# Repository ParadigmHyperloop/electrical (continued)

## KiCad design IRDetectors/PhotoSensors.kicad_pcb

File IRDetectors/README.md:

# About this Board

* **Owner:** @edhurtig
* **Status:** `Build`
* **Topic:** Research

## Design Abstract 

In the most basic sense, this board is an Arduino with support for 2 modulated IR emitters and paired receivers. They are essentially smart IR proximity sensors. 

## Purpose

These boards are intended to detect vertical strips (4" wide) that are placed every 100' on the hypertube walls. These strips are useful for navigation purposes and tell the pod where it is in the tube.

These boards are also somewhat of a prototype for a localized control module for subsystems like #brakes where a local uC receives commands from the main flight computer, but locally is the one responsible for controlling the state of the brake control solenoids, monitoring pressures and temperatures, etc.

## Tech Specs

- **Microcontroller** Atmega32U4
- **Communication** 1 Micro USB, 1 ISP Header, 1 RS485 bus, I2C, (maybe) CANbus
- **Sensors** 2 IR Emitters, 2 IR Receivers. Local hardware-based 36Khz IR modulator.
- **Expansion Headers** All unused Atmega inputs and outputs routed to an expansion header

### RS485 Details
There are 3 ports that all share the RS485 connection: 2x Ethernet jacks (for daisy chain), 1x 4 pin Phoenix contact port

### Power Details

This board is a 5V logic level board. The board may be powered over USB or via an external power source. The external power source is recommended at 5.5V. Do not exceed 12V on any of the external power inputs.

### External Power Inputs

Power may be supplied through the 2 pin Phoenix Contact Power Connector as labeled on the board's silkscreen.

Alternatively, power may be supplied via the RJ45 jacks by supplying 5.5-12V on pin 8, and Ground on pin 7.  The jumpers for VCOM power and VCOM GND must be stuffed in order to enable power via the Ethernet ports.

**Do not plug these boards into a standard ethernet switch, behavior is undefined**

### On-Board Documentation (Silkscreen)
```
5V Logic
VCC Regulated 5V
VCOM Recommended 5.5V

Ethernet Pinout:
1-2: RS485 RX - / +
3: External IR Sync
4-5: RS485 TX - / +
6: Passthrough
7: VCOM - (Ground)
8: VCOM + (5-12V DC)

VCOM PWR set jumpers 
GND EN & VCOM EN 
```
## Status

- **Rev 1A** was ordered and lost in transit 😢 
- **Rev 1B** was ordered and partially assembled. The first board is currently in a state were it powers on. Next step is to plug in an ISP and flash a bootloader onto the Atmega.

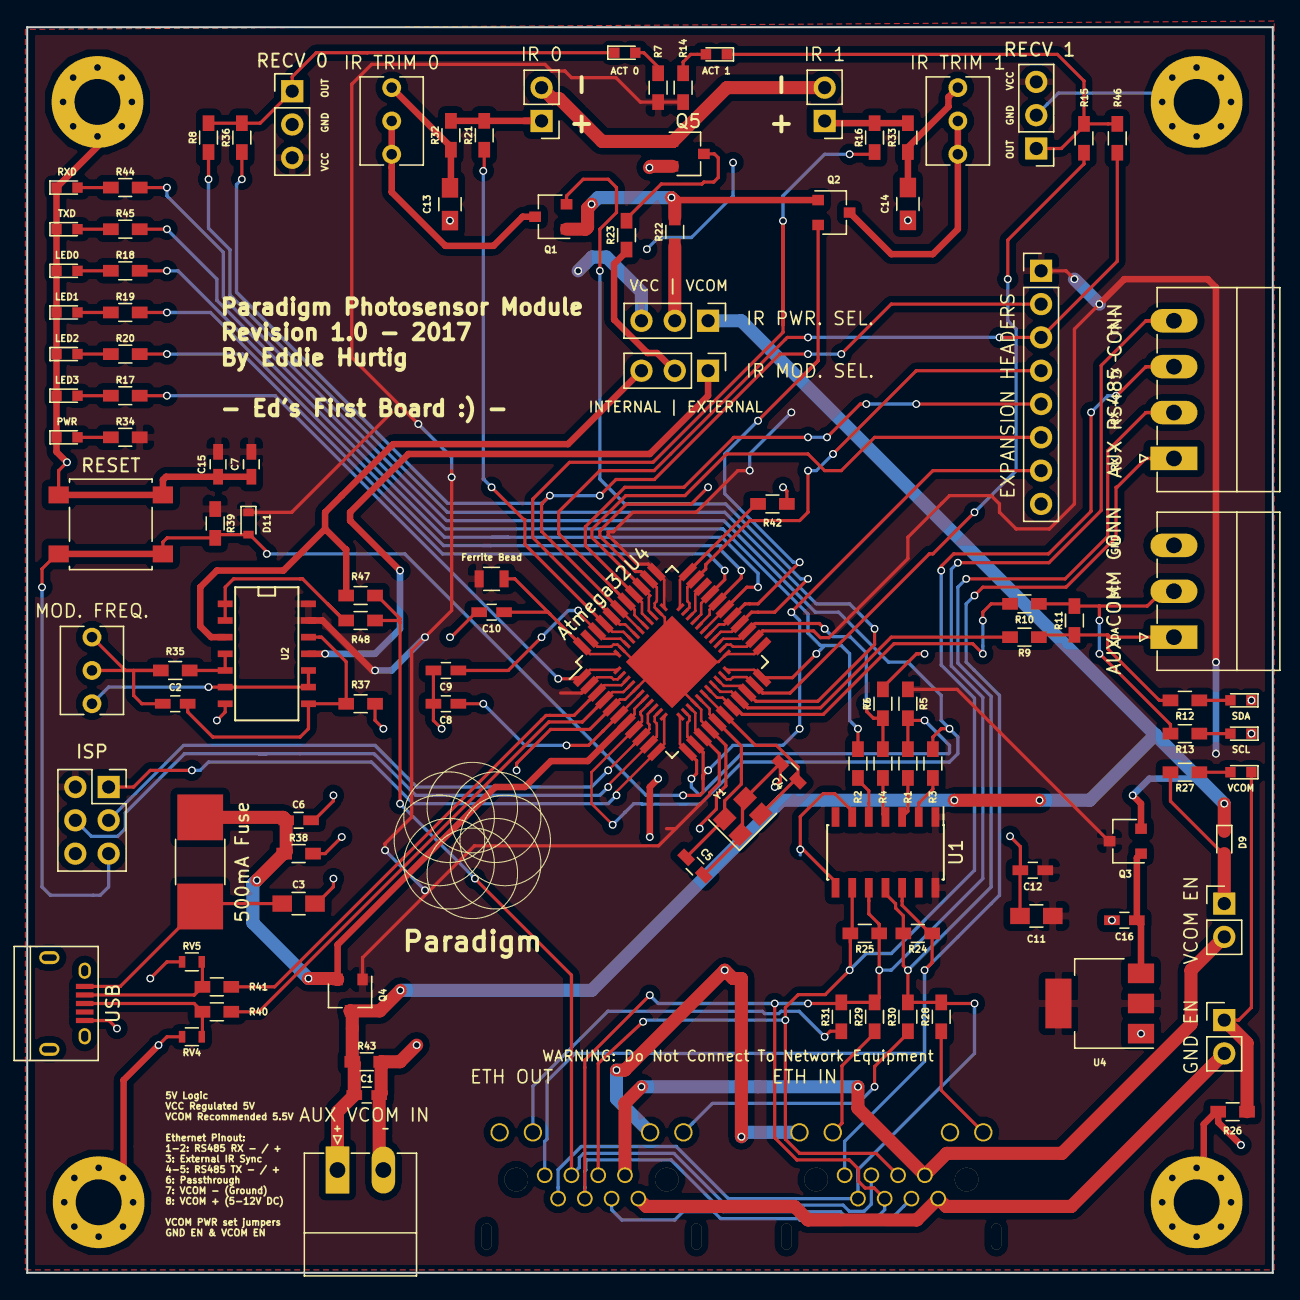
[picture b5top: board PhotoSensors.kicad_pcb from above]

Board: 2 copper layers, 95.0 x 95.0 mm, 112 parts (0 on the bottom side), 92 nets.

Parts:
500mA Fuse: 500mA; R_1812_HandSoldering
ACT 0: D0_ACT; LED_0603
ACT 1: D1_ACT; LED_0603
AUX COMM CONN: I2C _CONN; PhoenixContact_MC-G_03x3.50mm_Angled
AUX RS485 CONN: RS485_CONN; PhoenixContact_MC-G_04x3.50mm_Angled
AUX VCOM IN: PWR_IN; PhoenixContact_MC-G_02x3.50mm_Angled
Atmega32U4: ATMEGA32U4RC-A; QFN-44_7x7mm_Combined_TQFP-44_10x10mm_Pitch0.8mm
C1, C2: 10n; C_0603_HandSoldering
C3, C11: 22u; C_0805_HandSoldering
C4, C5: 22p; C_0603_HandSoldering
C6, C7, C9, C12, C15, C16: 100n; C_0603_HandSoldering
C8, C10: 1u; C_0603_HandSoldering
C13, C14: 10u; C_0805_HandSoldering
D9: D_VCOM; D_0603
D11: D_RST; D_0603
EXPANSION HEADERS: CONN_01X08; Pin_Header_Straight_1x08_Pitch2.54mm
Ferrite Bead: Ferrite_Bead; R_0805
GND EN: GND_EN; Pin_Header_Straight_1x02_Pitch2.54mm
IR 0: CONN_IR0; Pin_Header_Straight_1x02_Pitch2.54mm
IR 1: CONN_IR1; Pin_Header_Straight_1x02_Pitch2.54mm
IR MOD. SEL.: IR_SYNC_SELECT; Pin_Header_Straight_1x03_Pitch2.54mm
IR PWR. SEL.: Emitter Current Source; Pin_Header_Straight_1x03_Pitch2.54mm
IR TRIM 0, IR TRIM 1: RP500; Potentiometer_Trimmer_Vishay_T73XW_Vertical
ISP: ISP; Socket_Strip_Straight_2x03_Pitch2.54mm
J1, J2: RJ45_LEDS; RJ45_8P8C_90DEG_LEDs
LED0: LED1; LED_0603
LED1: LED2; LED_0603
LED2: LED3; LED_0603
LED3: LED0; LED_0603
MOD. FREQ.: POT_TRIM; Potentiometer_Trimmer_Vishay_T73XW_Vertical
PWR: PWR_LED; LED_0603
Q1, Q2, Q4: FDN340PCT-ND; SC-59
Q3: FDN340PCT; SC-59
Q5: Q_PMOS_SDG; SC-59
R1, R2, R3, R4, R16, R21, R23, R26, R32, R33, R36, R46, R48: 0; R_0603_HandSoldering
R5, R6: 20k; R_0603_HandSoldering
R7, R12, R13, R14, R17, R18, R19, R20, R27, R28, R29, R30, R31, R34, R44, R45: 1k; R_0603_HandSoldering
R8, R15: 220; R_0603_HandSoldering
R9, R10, R11, R47: DNS; R_0603_HandSoldering
R22: 470; R_0603_HandSoldering
R24, R25: 120; R_0603_HandSoldering
R35: 100k; R_0603_HandSoldering
R37, R38, R39, R42, R43: 10k; R_0603_HandSoldering
R40, R41: 22R; R_0603_HandSoldering
RECV 0: CONN_PD0; Pin_Header_Straight_1x03_Pitch2.54mm
RECV 1: CONN_PD1; Pin_Header_Straight_1x03_Pitch2.54mm
RESET: RESET_BTN; SW_SPST_B3S-1000
RV4, RV5: CG0603MLC; R_0603
RXD: RX_LED; LED_0603
SCL: SCL; LED_0603
SDA: SDA; LED_0603
TXD: TX_LED; LED_0603
U1: MAX13432EETD; SOIC-14_3.9x8.7mm_Pitch1.27mm
U2: 7400; SOIC-14_N
U4: NCP1117ST50T3GOSCT; SOT-223
USB: USB_MICRO; USB_Micro-B
VCOM: VCOM_PWR; LED_0603
VCOM EN: VCOM_EN; Pin_Header_Straight_1x02_Pitch2.54mm
Y1: Crystal; Crystal_SMD_Abracon_ABM8G-4pin_3.2x2.5mm

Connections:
/ADC4: Atmega32U4.39, EXPANSION HEADERS.2, R36.1
/ADC5: Atmega32U4.38, EXPANSION HEADERS.3, R46.1
/Atmega/D+: Atmega32U4.4, R40.1
/Atmega/D-: Atmega32U4.3, R41.1
/Atmega/MISO: Atmega32U4.11, ISP.1
/Atmega/MOSI: Atmega32U4.10, ISP.4
/Atmega/PC7: Atmega32U4.32, EXPANSION HEADERS.4
/Atmega/PF6: Atmega32U4.37, EXPANSION HEADERS.5
/Atmega/PF7: Atmega32U4.36, EXPANSION HEADERS.6
/Atmega/SCK: Atmega32U4.9, ISP.3
/Atmega/XTAL1: Atmega32U4.17, C4.1, Y1.2
/Atmega/XTAL2: Atmega32U4.16, C5.1, Y1.4
/D0_OUT: ACT 0.1, R8.2, R36.2, RECV 0.1
/D1_OUT: ACT 1.1, R15.2, R46.2, RECV 1.1
/DE: Atmega32U4.12, R1.1, R5.1
/EXT_SYNC: J1.3, J2.3, R47.1, R48.1
/INT0: Atmega32U4.20, R8.1
/INT1: Atmega32U4.21, R15.1
/IR0_+: IR 0.1, R21.2, R32.2
/IR0_-: IR 0.2, IR 1.2, Q5.1
/IR0_ADC: Atmega32U4.41, R21.1
/IR0_SETPOINT: Atmega32U4.26, Q1.2
/IR1_+: IR 1.1, R16.1, R33.2
/IR1_ADC: Atmega32U4.40, R16.2
/IR1_SETPOINT: Atmega32U4.27, Q2.2
/LED0: Atmega32U4.1, R17.2
/LED1: Atmega32U4.28, R18.2
/LED2: Atmega32U4.29, R19.2
/LED3: Atmega32U4.30, R20.2
/RE: Atmega32U4.25, R4.1, R6.2
/RESET: Atmega32U4.13, D11.2, EXPANSION HEADERS.7, ISP.5, R39.2, RESET.2
/RS422_Transiever/DE: R1.2, U1.3
/RS422_Transiever/RE: R4.2, U1.4
/RS422_Transiever/RS485_RX_+: AUX RS485 CONN.2, J1.2, J2.2, R24.1, R28.2, R30.2, U1.11
/RS422_Transiever/RS485_RX_-: AUX RS485 CONN.1, J1.1, J2.1, R24.2, U1.12
/RS422_Transiever/RS485_TX_+: AUX RS485 CONN.4, J1.4, J2.4, R25.1, R29.2, R31.2, U1.10
/RS422_Transiever/RS485_TX_-: AUX RS485 CONN.3, J1.5, J2.5, R25.2, U1.9
/RS422_Transiever/RXD: R3.2, U1.2
/RS422_Transiever/TXD: R2.2, U1.5
/RXD: Atmega32U4.8, R3.1, R44.2
/SCL: Atmega32U4.18, R10.2
/SDA: Atmega32U4.19, R9.2
/TXD: Atmega32U4.22, R2.1, R45.2
GND: AUX COMM CONN.3, AUX VCOM IN.2, Atmega32U4.5, Atmega32U4.15, Atmega32U4.23, Atmega32U4.35, Atmega32U4.43, C1.2, C3.2, C4.2, C5.2, C6.2, C7.1, C8.2, C9.2, C10.2, C11.2, C12.2, C13.1, C14.1, C15.1, C16.2, EXPANSION HEADERS.8, ISP.6, J1.9, J1.11, J2.9, J2.11, LED0.1, LED1.1, LED2.1, LED3.1, PWR.1, Q5.2, R6.1, R26.2, R37.2, R38.2, R42.1, R43.1, RECV 0.2, RECV 1.2, RESET.1, RV4.1, RV5.1, RXD.1, SCL.1, SDA.1, TXD.1, U1.6, U1.8, U2.7, U4.1, USB.5, USB.6, Y1.1, Y1.3
unnamed: C2.1, MOD. FREQ..1, MOD. FREQ..2, R35.1
unnamed: C2.2, R37.1, U2.8, U2.12
unnamed: 500mA Fuse.2, C3.1, USB.1
unnamed: Atmega32U4.6, C8.1
unnamed: Atmega32U4.42, C9.1
unnamed: Atmega32U4.44, C10.1, Ferrite Bead.1
unnamed: C13.2, IR TRIM 0.3, R32.1
unnamed: C14.2, IR TRIM 1.3, R33.1
unnamed: C16.1, Q3.1, U4.3
unnamed: ACT 0.2, R7.2
unnamed: R12.2, SDA.2
unnamed: R13.2, SCL.2
unnamed: ACT 1.2, R14.2
unnamed: LED3.2, R17.1
unnamed: LED0.2, R18.1
unnamed: LED1.2, R19.1
unnamed: LED2.2, R20.1
unnamed: D9.2, R27.2, VCOM EN.1
unnamed: GND EN.1, R26.1, VCOM.1
unnamed: R27.1, VCOM.2
unnamed: PWR.2, R34.1
unnamed: R44.1, RXD.2
unnamed: R45.1, TXD.2
unnamed: MOD. FREQ..3, U2.6, U2.9, U2.10
unnamed: J1.7, J2.7, VCOM EN.2
unnamed: GND EN.2, J1.8, J2.8
unnamed: J1.10, R29.1
unnamed: J1.12, R28.1
unnamed: J2.10, R31.1
unnamed: J2.12, R30.1
unnamed: IR PWR. SEL..2, R22.1
unnamed: IR MOD. SEL..1, U2.11
unnamed: IR MOD. SEL..2, R23.1
unnamed: IR MOD. SEL..3, R47.2, U2.3
unnamed: AUX COMM CONN.1, R9.1, R11.1, R12.1
unnamed: AUX COMM CONN.2, R10.1, R11.2, R13.1
unnamed: R41.2, RV5.2, USB.2
unnamed: R40.2, RV4.2, USB.3
unnamed: Q1.1, Q2.1, R22.2
unnamed: IR TRIM 0.1, IR TRIM 0.2, Q1.3
unnamed: IR TRIM 1.1, IR TRIM 1.2, Q2.3
unnamed: Q5.3, R23.2
unnamed: R35.2, U2.4, U2.5
unnamed: Atmega32U4.33, R42.2
unnamed: R48.2, U2.1, U2.2
VCC: Atmega32U4.2, Atmega32U4.14, Atmega32U4.24, Atmega32U4.34, C7.2, C11.1, C12.1, C15.2, D11.1, EXPANSION HEADERS.1, Ferrite Bead.2, IR PWR. SEL..3, ISP.2, Q3.3, Q4.1, R5.2, R7.1, R14.1, R34.2, R39.1, RECV 0.3, RECV 1.3, U1.1, U1.14, U2.13, U2.14, U4.2, U4.4
VCOM: AUX VCOM IN.1, C1.1, D9.1, IR PWR. SEL..1, Q3.2, Q4.3, R43.2
VUSB: 500mA Fuse.1, Atmega32U4.7, C6.1, Q4.2, R38.1

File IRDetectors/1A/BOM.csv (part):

Component,Description,Part,References,Value,Footprint,Quantity Per PCB,Datasheet,Supporting,
1,Unpolarized capacitor,C,C6 C7 C9 C12 C15 C16,100n,C_0603_HandSoldering,6,https://www.digikey.com/product-detail/en/murata-electronics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,https://www.digikey.com/product-detail/en/murata-electronics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,
2,Unpolarized capacitor,C,C1 C2,10n,C_0603_HandSoldering,2,https://www.digikey.com/product-detail/en/murata-electronics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,https://www.digikey.com/product-detail/en/murata-electronics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,
3,Unpolarized capacitor,C,C13 C14,10u,C_0805_HandSoldering,2,https://www.digikey.com/product-detail/en/murata-electronics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,https://www.digikey.com/product-detail/en/murata-electronics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,
4,Unpolarized capacitor,C,C8 C10,1u,C_0603_HandSoldering,2,https://www.digikey.com/product-detail/en/samsung-electro-me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,https://www.digikey.com/product-detail/en/samsung-electro-me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,
5,Unpolarized capacitor,C,C4 C5,22p,C_0603_HandSoldering,2,https://www.digikey.com/product-detail/en/samsung-electro-me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,https://www.digikey.com/product-detail/en/samsung-electro-me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,
6,Polarised capacitor,CP,C11,22u,C_0805_HandSoldering,1,https://www.digikey.com/product-detail/en/avx-corporation/F9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,https://www.digikey.com/product-detail/en/avx-corporation/F9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,
7,Unpolarized capacitor,C,C3,22u,C_0805_HandSoldering,1,https://www.digikey.com/product-detail/en/samsung-electro-me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,https://www.digikey.com/product-detail/en/samsung-electro-me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,
8,LED generic,LED,D1,D0_ACT,LED_0603,1,https://www.digikey.com/product-detail/en/wurth-electronics-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,https://www.digikey.com/product-detail/en/wurth-electronics-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,
9,LED generic,LED,D4,D1_ACT,LED_0603,1,https://www.digikey.com/product-detail/en/wurth-electronics-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,https://www.digikey.com/product-detail/en/wurth-electronics-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,
10,Diode,D,D11,D_RST,D_0603,1,https://www.digikey.com/product-detail/en/avx-corporation/SD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,https://www.digikey.com/product-detail/en/avx-corporation/SD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,
11,Diode,D,D9,D_VCOM,D_0603,1,https://www.digikey.com/product-detail/en/avx-corporation/SD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,https://www.digikey.com/product-detail/en/avx-corporation/SD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,
12,LED generic,LED,D5,LED0,LED_0603,1,https://www.digikey.com/product-detail/en/wurth-electronics-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,https://www.digikey.com/product-detail/en/wurth-electronics-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,
13,LED generic,LED,D6,LED1,LED_0603,1,https://www.digikey.com/product-detail/en/wurth-electronics-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,https://www.digikey.com/product-detail/en/wurth-electronics-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,
14,LED generic,LED,D7,LED2,LED_0603,1,https://www.digikey.com/product-detail/en/wurth-electronics-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,https://www.digikey.com/product-detail/en/wurth-electronics-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,
15,LED generic,LED,D8,LED3,LED_0603,1,https://www.digikey.com/product-detail/en/wurth-electronics-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,https://www.digikey.com/product-detail/en/wurth-electronics-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,
16,LED generic,LED,D12,PWR_LED,LED_0603,1,https://www.digikey.com/product-detail/en/wurth-electronics-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,https://www.digikey.com/product-detail/en/wurth-electronics-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,
17,LED generic,LED,D13,RX_LED,LED_0603,1,https://www.digikey.com/product-detail/en/wurth-electronics-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,https://www.digikey.com/product-detail/en/wurth-electronics-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,
18,LED generic,LED,D3,SCL,LED_0603,1,https://www.digikey.com/product-detail/en/wurth-electronics-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,https://www.digikey.com/product-detail/en/wurth-electronics-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,
19,LED generic,LED,D2,SDA,LED_0603,1,https://www.digikey.com/product-detail/en/wurth-electronics-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,https://www.digikey.com/product-detail/en/wurth-electronics-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,
20,LED generic,LED,D14,TX_LED,LED_0603,1,https://www.digikey.com/product-detail/en/wurth-electronics-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,https://www.digikey.com/product-detail/en/wurth-electronics-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,
21,LED generic,LED,D10,VCOM_PWR,LED_0603,1,https://www.digikey.com/product-detail/en/wurth-electronics-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,https://www.digikey.com/product-detail/en/wurth-electronics-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,
22,"Fuse, generic",Fuse,F500,500mA,R_1812_HandSoldering,1,https://www.digikey.com/product-detail/en/bourns-inc/MF-MSMF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,https://www.digikey.com/product-detail/en/bourns-inc/MF-MSMF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,
23,Trim-Potentionmeter,POT_TRIM,FREQ1,POT_TRIM,Potentiometer_Trimmer_Vishay_T73XW_Vertical,1,https://www.digikey.com/product-detail/en/vishay-spectrol/M6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,https://www.digikey.com/product-detail/en/vishay-spectrol/M6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,
24,"RJ45, status leds",RJ45_LEDS,J1 J2,RJ45_LEDS,RJ45_8P8C_90DEG_LEDs,2,https://www.digikey.com/product-detail/en/amphenol-commercia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,https://www.digikey.com/product-detail/en/amphenol-commercia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,
25,"Dual Jumper, normally closed",Jumper_NC_Dual,JP3,Emitter Current Source,Pin_Header_Straight_1x03_Pitch2.54mm,1,https://www.digikey.com/product-detail/en/amphenol-fci/68000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,https://www.digikey.com/product-detail/en/amphenol-fci/68000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,
26,"Jumper, normally closed",Jumper_NC_Small,JP2,GND_EN,Pin_Header_Straight_1x02_Pitch2.54mm,1,https://www.digikey.com/product-detail/en/amphenol-fci/67996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,https://www.digikey.com/product-detail/en/amphenol-fci/67996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,
27,"Dual Jumper, normally closed",Jumper_NC_Dual,JP4,IR_SYNC_SELECT,Pin_Header_Straight_1x03_Pitch2.54mm,1,,,
28,"Jumper, normally closed",Jumper_NC_Small,JP1,VCOM_EN,Pin_Header_Straight_1x02_Pitch2.54mm,1,,,
29,Ferrite bead,Ferrite_Bead,MH2029-300Y1,Ferrite_Bead,R_0805,1,https://www.digikey.com/product-detail/en/bourns-inc/MH2029-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,https://www.digikey.com/product-detail/en/bourns-inc/MH2029-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,
30,"Connector, single row, 01x08",CONN_01X08,P4,CONN_01X08,Pin_Header_Straight_1x08_Pitch2.54mm,1,,,
31,"Connector, single row, 01x02",CONN_01X02,P6,CONN_IR0,Pin_Header_Straight_1x02_Pitch2.54mm,1,,,
32,"Connector, single row, 01x02",CONN_01X02,P5,CONN_IR1,Pin_Header_Straight_1x02_Pitch2.54mm,1,,,
33,"Connector, single row, 01x03",CONN_01X03,P2,CONN_PD0,Pin_Header_Straight_1x03_Pitch2.54mm,1,,,
34,"Connector, single row, 01x03",CONN_01X03,P1,CONN_PD1,Pin_Header_Straight_1x03_Pitch2.54mm,1,,,
35,"Connector, single row, 01x03",CONN_01X03,P3,I2C _CONN,PhoenixContact_MC-G_03x3.50mm_Angled,1,https://www.digikey.com/product-detail/en/molex-llc/03950210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,https://www.digikey.com/product-detail/en/molex-llc/03950210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,https://www.digikey.com/product-detail/en/molex-llc/03950000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
36,"Connector, double row, 02x03",CONN_02X03,P10,ISP,Socket_Strip_Straight_2x03_Pitch2.54mm,1,,,
37,"Connector, single row, 01x02",CONN_01X02,P7,PWR_IN,PhoenixContact_MC-G_02x3.50mm_Angled,1,https://www.digikey.com/product-detail/en/molex-llc/03950210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,https://www.digikey.com/product-detail/en/molex-llc/03950210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,https://www.digikey.com/product-detail/en/molex-llc/39500-00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
38,"Connector, single row, 01x04",CONN_01X04,P8,RS485_CONN,PhoenixContact_MC-G_04x3.50mm_Angled,1,https://www.digikey.com/product-detail/en/molex-llc/03950210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,https://www.digikey.com/product-detail/en/molex-llc/03950210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,https://www.digikey.com/product-detail/en/molex-llc/39500-00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
39,USB micro/mini connector,USB_OTG,P9,USB_MICRO,USB_Micro-B,1,https://www.digikey.com/product-detail/en/amphenol-fci/10118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,https://www.digikey.com/product-detail/en/amphenol-fci/10118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,
40,Transistor P-MOSFET with substrate diode (general),Q_PMOS_SDG,Q3,FDN340PCT,SC-59,1,https://www.digikey.com/product-detail/en/fairchild-on-semic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,https://www.digikey.com/product-detail/en/fairchild-on-semic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,
41,Transistor N-JFET (general),Q_NJFET_DGS,Q1 Q2,FDN340PCT-ND,SC-59,2,https://www.digikey.com/product-detail/en/fairchild-on-semic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,https://www.digikey.com/product-detail/en/fairchild-on-semic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,
42,Transistor P-MOSFET with substrate diode (general),Q_PMOS_SDG,Q4,FDN340PCT-ND,SC-59,1,https://www.digikey.com/product-detail/en/fairchild-on-semic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,https://www.digikey.com/product-detail/en/fairchild-on-semic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,
43,Resistor,R,R1 R2 R3 R4 R16 R21 R23 R26 R32 R33 R36 R46 R48,0,R_0603_HandSoldering,13,https://www.digikey.com/product-detail/en/yageo/RC0603JR-070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,https://www.digikey.com/product-detail/en/yageo/RC0603JR-070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,
44,Resistor,R,R35,100k,R_0603_HandSoldering,1,https://www.digikey.com/product-detail/en/yageo/RC0603JR-071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,https://www.digikey.com/product-detail/en/yageo/RC0603JR-071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,
45,Resistor,R,R37 R38 R39 R42 R43,10k,R_0603_HandSoldering,5,https://www.digikey.com/product-detail/en/yageo/RC0603JR-071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,https://www.digikey.com/product-detail/en/yageo/RC0603JR-071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,
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
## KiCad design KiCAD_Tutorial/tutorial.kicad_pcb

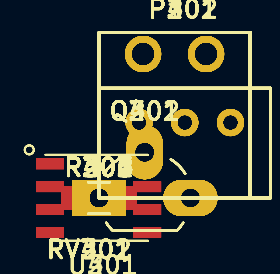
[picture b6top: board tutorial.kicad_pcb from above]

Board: 2 copper layers, 40 parts (0 on the bottom side), 32 nets, no tracks yet.

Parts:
P101, P201, P202, P301, P302, P401, P402: CONN_01X02; CONN_PHOENIX_1844210_2PIN
Q201, Q202, Q301, Q302, Q401, Q402: Transistor_PNP_MicroCommCo_2N3906; TO-92_Rugged_swap2and3
R201, R204, R301, R304, R401, R404: 1k; R_0805_HandSoldering
R202, R205, R302, R305, R402, R405: 10k; R_0805_HandSoldering
R203, R206, R303, R306, R403, R406: 10; R_0805_HandSoldering
RV201, RV202, RV301, RV302, RV401, RV402: 5k; BOURNS_MULTITURNPOT_3PIN
U201, U301, U401: OpAmp_TexasInstruments_LM358DR; SOIC-8_3.10x3.10_Pitch0.65mm

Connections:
+5V: P101.1, R203.1, R206.1, R303.1, R306.1, R403.1, R406.1, RV201.1, RV202.1, RV301.1, RV302.1, RV401.1, RV402.1, U201.8, U301.8, U401.8
GND: P101.2, P201.2, P202.2, P301.2, P302.2, P401.2, P402.2, R202.2, R205.2, R302.2, R305.2, R402.2, R405.2, RV201.3, RV202.3, RV301.3, RV302.3, RV401.3, RV402.3, U201.4, U301.4, U401.4
unnamed: P201.1, Q201.1
unnamed: P202.1, Q202.1
unnamed: P301.1, Q301.1
unnamed: P302.1, Q302.1
unnamed: P401.1, Q401.1
unnamed: P402.1, Q402.1
unnamed: Q201.2, R203.2
unnamed: Q201.3, R201.2, U201.1
unnamed: Q202.2, R206.2
unnamed: Q202.3, R204.2, U201.7
unnamed: Q301.2, R303.2
unnamed: Q301.3, R301.2, U301.1
unnamed: Q302.2, R306.2
unnamed: Q302.3, R304.2, U301.7
unnamed: Q401.2, R403.2
unnamed: Q401.3, R401.2, U401.1
unnamed: Q402.2, R406.2
unnamed: Q402.3, R404.2, U401.7
unnamed: R201.1, R202.1, U201.2
unnamed: R204.1, R205.1, U201.6
unnamed: R301.1, R302.1, U301.2
unnamed: R304.1, R305.1, U301.6
unnamed: R401.1, R402.1, U401.2
unnamed: R404.1, R405.1, U401.6
unnamed: RV201.2, U201.3
unnamed: RV202.2, U201.5
unnamed: RV301.2, U301.3
unnamed: RV302.2, U301.5
unnamed: RV401.2, U401.3
unnamed: RV402.2, U401.5

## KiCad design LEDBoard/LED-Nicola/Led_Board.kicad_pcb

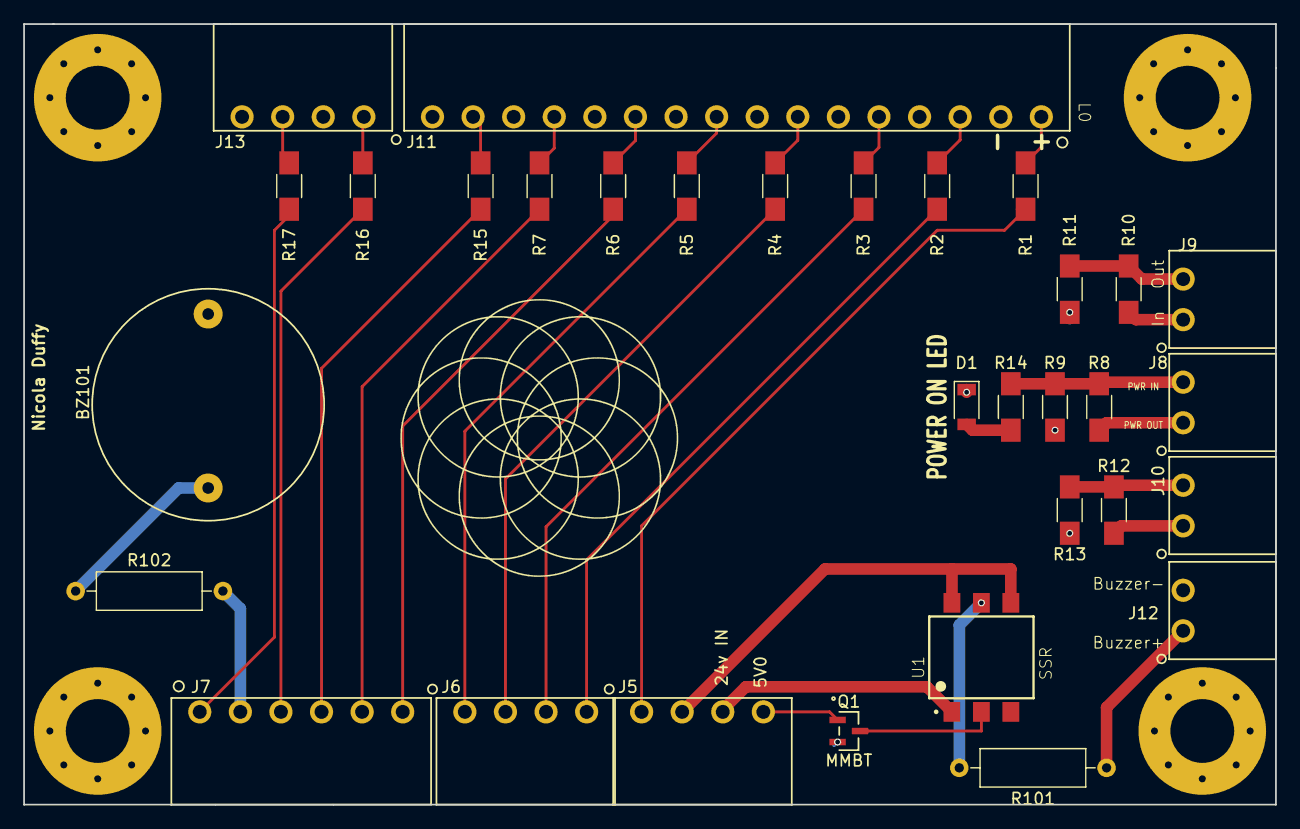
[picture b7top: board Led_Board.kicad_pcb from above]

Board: 2 copper layers, 107.9 x 67.3 mm, 36 parts (0 on the bottom side), 36 nets.

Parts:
BZ101: nicolaBuzzer
D1: D_1206
J1, J2, J3, J4: MountingHole_5.5mm_Pad_Via
J5, J6, J13: CONN_PHOENIX_1844236_4PIN
J7: CONN_PHOENIX_1844252_6PIN
J8, J9, J10, J12: CONN_PHOENIX_1844210_2PIN
J11: CONN_PHOENIX_1844359_16PIN
Q1: MMBT; MMBF170LT1G
R1, R2, R3, R4, R5, R6, R7, R8, R9, R10, R11, R12, R13, R14, R15, R16, R17: R_1206_HandSoldering
R101, R102: R_Axial_DIN0309_L9.0mm_D3.2mm_P12.70mm_Horizontal
U1: SSR; SOIC254P1005X390-6N

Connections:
/5V: J7.2, R102.2
/5V0: J5.3, U1.1
/24V: J5.2, U1.4, U1.6
/A0: J5.1, R1.2
/A1: J6.4, R2.2
/A2: J6.3, R3.2
/A3: J6.2, R4.2
/A4: J6.1, R5.2
/A5: J7.6, R6.2
/A6: J7.5, R7.2
/A7: J7.4, R15.2
/A8: J7.3, R16.2
/ArduinoLED: J7.1, R17.2
/Buzzer: J12.1, R101.1
/GND: BZ101.2, D1.1, J1.1, J2.1, J3.1, J4.1, J11.2, J11.4, J11.6, J11.8, J11.10, J11.12, J11.14, J11.16, J12.2, J13.2, J13.4, Q1.2, R9.2, R11.2, R13.2
/L0: J11.1, R1.1
/L1: J11.3, R2.1
/L2: J11.5, R3.1
/L3: J11.7, R4.1
/L4: J11.9, R5.1
/L5: J11.11, R6.1
/L6: J11.13, R7.1
/L7: J11.15, R15.1
/L8: J13.1, R16.1
/L9: J13.3, R17.1
/Transistor: J5.4, Q1.1
/VDI0: J8.1, R8.1
/VDI1: J9.1, R10.1
/VDI2: J10.1, R12.1
/VDO0: J8.2, R8.2, R9.1, R14.1
/VDO1: J9.2, R10.2, R11.1
/VDO2: J10.2, R12.2, R13.1
unnamed: BZ101.1, R102.1
unnamed: D1.2, R14.2
unnamed: Q1.3, U1.2
unnamed: R101.2, U1.5

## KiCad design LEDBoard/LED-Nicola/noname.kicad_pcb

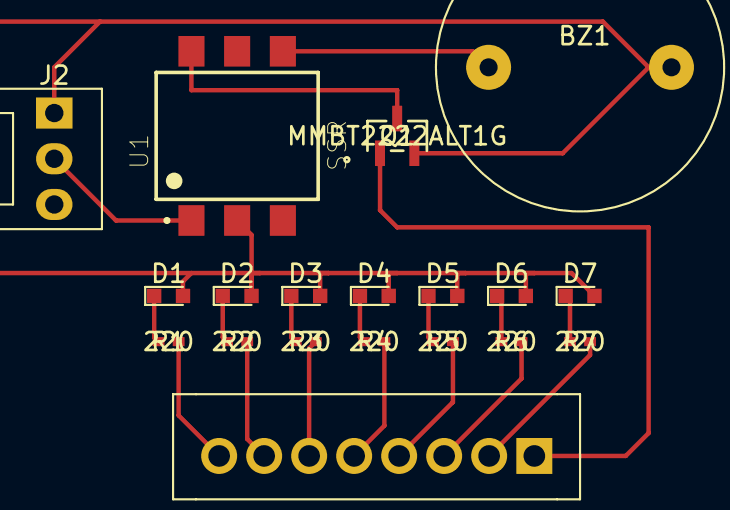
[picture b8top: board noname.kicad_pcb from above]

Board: 2 copper layers, 19 parts (0 on the bottom side), 19 nets.

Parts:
BZ1: Buzzer; BUZZER
D1, D2, D3, D4, D5, D6, D7: LED; LED_0603
J1: CONN_01X08; Wafer_Vertical22.5x5.8x7RM2.5-8
J2: CONN_01X03; Fan_Pin_Header_Straight_1x03
Q1: MMBT2222ALT1G; MMBF170LT1G
R1, R2, R3, R4, R5, R6, R7: 220; RC0402FR-072K2L
U1: SSR; SOIC254P1005X390-6N

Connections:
/24V: J2.2, U1.1
/A0: J1.8, R1.2
/A1: J1.7, R2.2
/A2: J1.6, R3.2
/A3: J1.5, R4.2
/A4: J1.4, R5.2
/A5: J1.3, R6.2
/A6: J1.2, R7.2
/A7: J1.1, Q1.1
/Collector: Q1.3, U1.6
/buzzer: BZ1.1, U1.4
GND: BZ1.2, D1.2, D2.2, D3.2, D4.2, D5.2, D6.2, D7.2, J2.1, Q1.2, U1.2
unnamed: D1.1, R1.1
unnamed: D2.1, R2.1
unnamed: D3.1, R3.1
unnamed: D4.1, R4.1
unnamed: D5.1, R5.1
unnamed: D6.1, R6.1
unnamed: D7.1, R7.1
